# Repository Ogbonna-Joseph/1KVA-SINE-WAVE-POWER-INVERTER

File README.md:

# 1KVA-SINE-WAVE-POWER-INVERTER
This is a design of a sine wave power inverter, which can be used in your homes and offices.

IN the design the Inverter converts 12v/24v to 220volts.

# SECTIONS OF THE DESIGN
- Power Section : This consist of the battery portion, here we used 12v acid battery to power it on.
- Oscillator : This is the part that the frequency and signals are  being generation to feed to the MOSFET.
- Booster : This involves the mosfet switching the signal state and giving to the transmorfer.
- Output : Here the transformer gives an output of 220volts..

# SCHEMATICS OF PCB BOARD

#  PCB ROUTE SECTION

# PCB BOARD

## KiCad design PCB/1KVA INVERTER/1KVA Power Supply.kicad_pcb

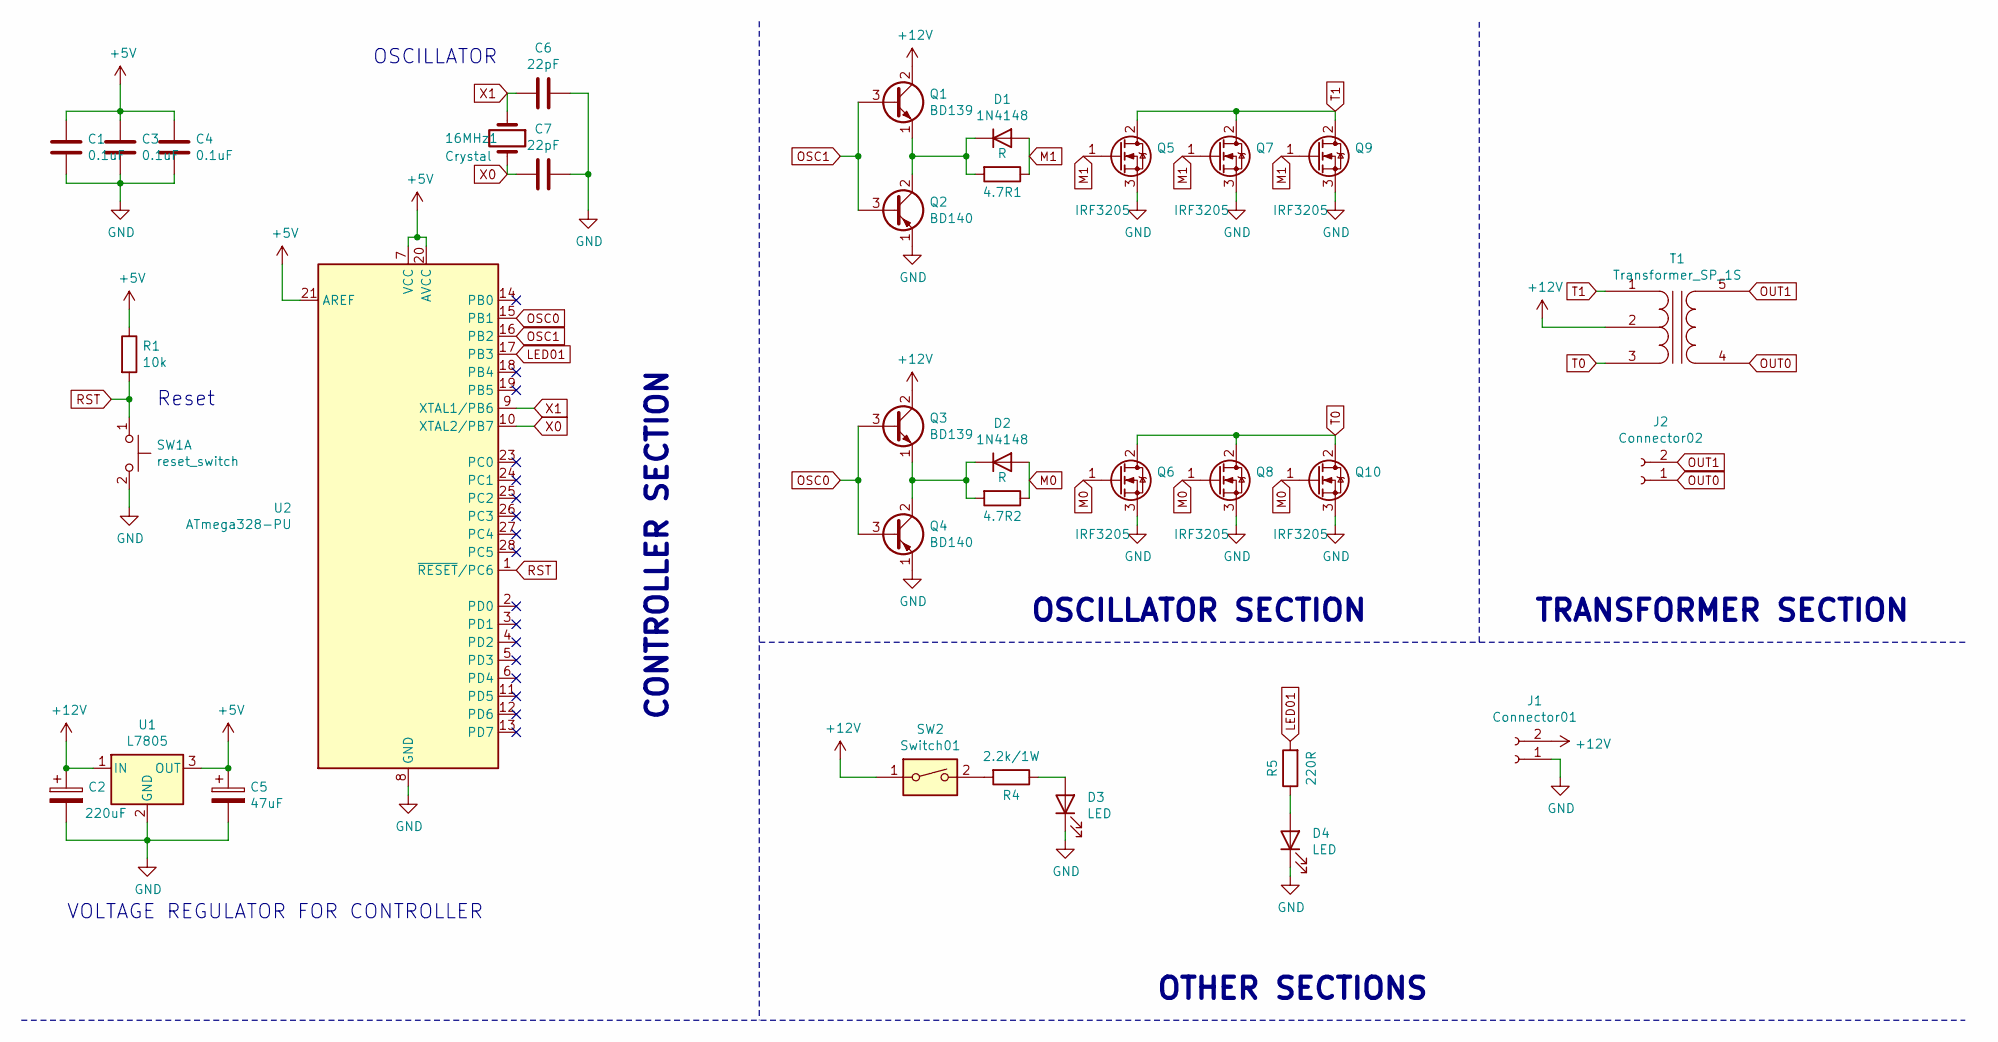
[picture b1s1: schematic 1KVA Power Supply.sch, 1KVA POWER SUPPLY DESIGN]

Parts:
4.7R1, 4.7R2: R; R_Axial_DIN0414_L11.9mm_D4.5mm_P15.24mm_Horizontal
16MHz1: Crystal; Crystal_HC49-4H_Vertical
C1: 0.1uF; C_Disc_D3.0mm_W2.0mm_P2.50mm
C2: 220uF; CP_Radial_D4.0mm_P1.50mm
C3, C4: 0.1uF; C_Disc_D3.0mm_W1.6mm_P2.50mm
C5: 47uF; CP_Radial_D5.0mm_P2.00mm
C6, C7: 22pF; C_Disc_D3.0mm_W2.0mm_P2.50mm
D1, D2: 1N4148; D_DO-35_SOD27_P7.62mm_Horizontal
D3: LED; LED_D3.0mm
D4: LED; LED_D3.0mm_Clear
J1: Connector01; JST_EH_S2B-EH_1x02_P2.50mm_Horizontal
J2: Connector02; JST_EH_S2B-EH_1x02_P2.50mm_Horizontal
Q1, Q3: BD139; TO-126-3_Vertical
Q2, Q4: BD140; TO-126-3_Vertical
Q5, Q6, Q7, Q8, Q9, Q10: IRF3205; TO-220-3_Vertical
R1: 10k; R_Axial_DIN0414_L11.9mm_D4.5mm_P15.24mm_Horizontal
R4: 2.2k/1W; R_Axial_DIN0414_L11.9mm_D4.5mm_P15.24mm_Horizontal
R5: 220R; R_Axial_DIN0414_L11.9mm_D4.5mm_P15.24mm_Horizontal
SW1: reset_switch; SW_PUSH_6mm
SW2: Switch01; SW_DIP_SPSTx01_Slide_9.78x4.72mm_W7.62mm_P2.54mm
T1: Transformer_SP_1S; Transformer_MACOM_SM-22
U1: L7805; TO-220-3_Vertical
U2: ATmega328-PU; DIP-28_W7.62mm

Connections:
+5V: C1.1, C3.1, C4.1, C5.1, R1.1, U1.3 (OUT), U2.7 (VCC), U2.20 (AVCC), U2.21 (AREF)
+12V: C2.1, J1.2, Q1.2 (C), Q3.2 (C), SW2.1, T1.2 (PM), U1.1 (IN)
GND: C1.2, C2.2, C3.2, C4.2, C5.2, C6.1, C7.1, D3.1 (K), D4.1 (K), J1.1, Q2.1 (E), Q4.1 (E), Q5.3 (S), Q6.3 (S), Q7.3 (S), Q8.3 (S), Q9.3 (S), Q10.3 (S), SW1.2 (D), U1.2 (GND), U2.8 (GND), U2.22 (GND)
LED01: R5.2, U2.17 (PB3)
M0: 4.7R2.1, D2.2 (A), Q6.1 (G), Q8.1 (G), Q10.1 (G)
M1: 4.7R1.1, D1.2 (A), Q5.1 (G), Q7.1 (G), Q9.1 (G)
unnamed: 4.7R1.2, D1.1 (K), Q1.1 (E), Q2.2 (C)
unnamed: 4.7R2.2, D2.1 (K), Q3.1 (E), Q4.2 (C)
unnamed: D3.2 (A), R4.1
unnamed: D4.2 (A), R5.1
unnamed: R4.2, SW2.2
OSC0: Q3.3 (B), Q4.3 (B), U2.15 (PB1)
OSC1: Q1.3 (B), Q2.3 (B), U2.16 (PB2)
OUT0: J2.1, T1.4 (S1)
OUT1: J2.2, T1.5 (S2)
RST: R1.2, SW1.1 (C), U2.1 (~RESET~/PC6)
T0: Q6.2 (D), Q8.2 (D), Q10.2 (D), T1.3 (PR2)
T1: Q5.2 (D), Q7.2 (D), Q9.2 (D), T1.1 (PR1)
X0: 16MHz1.2, C7.2, U2.10 (XTAL2/PB7)
X1: 16MHz1.1, C6.2, U2.9 (XTAL1/PB6)

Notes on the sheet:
Reset
OSCILLATOR
VOLTAGE REGULATOR FOR CONTROLLER
CONTROLLER SECTION
OSCILLATOR SECTION
TRANSFORMER SECTION
OTHER SECTIONS

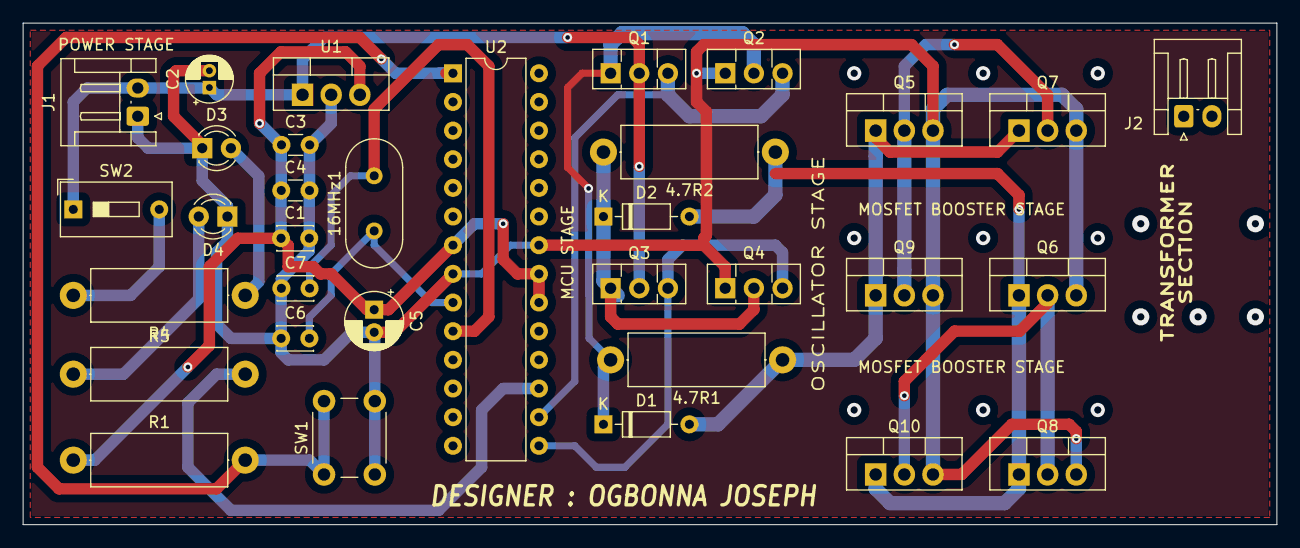
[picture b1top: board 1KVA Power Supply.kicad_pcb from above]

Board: 2 copper layers, 111.1 x 44.5 mm, 33 parts (0 on the bottom side), 18 nets.

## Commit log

2021-12-20 Create image
2021-12-20 Create Kicad
2021-12-23 Create main
2021-12-23 PCB DESIGN FILES
